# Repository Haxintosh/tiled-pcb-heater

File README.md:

# Tiled 3D printing bed
This project is a scalable, Klipper-compatible heated bed system designed for efficiency and flexibility. The bed is built from PCB-based heater tiles (≈100W each) that can be individually powered, allowing selective heating to reduce energy use. A central hub board, driven by an STM32 microcontroller, controls up to multiple channels with individual MOSFET switching and thermistor sensing.  

The project consists of 2 types of PCBs, the tiles and the power distribution boards.  

Currently there is a 150mm tile and a 8 channel power distribution board.  

## Images
Heater tile:  

Power distribution board:  

## Specs
The calculator can found here: https://www.desmos.com/calculator/dyaic1mb9s  

Per tile:
| Measurements 	| Value         	|
|--------------	|---------------	|
| Dimensions   	| 150mm x 150mm 	|
| Power			| ~110W @ 24v   	|
| Max Temp		| ~105°C*			|

> [!WARNING]
> The max operating temperature depends on the rated temperature of the connector. The thermal fuse blows at around 125°C to prevent thermal runaway, but the current chosen connector (MicroFit 3) is only rated to 105°C.

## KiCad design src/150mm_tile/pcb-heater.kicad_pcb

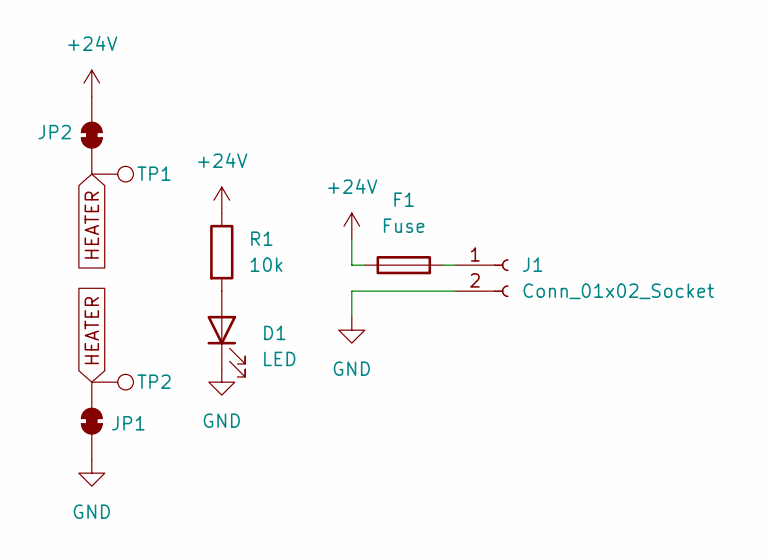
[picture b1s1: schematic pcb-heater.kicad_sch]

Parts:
D1: LED; LED_0603_1608Metric
F1: Fuse; thermal fuse
J1: Conn_01x02_Socket; Molex_Micro-Fit_3.0_43045-0218_2x01-1MP_P3.00mm_Vertical
JP1, JP2: SolderJumper_2_Bridged; SolderJumper-2_P1.3mm_Bridged_Pad1.0x1.5mm
R1: 10k; R_0603_1608Metric
TP1, TP2: TestPoint; TestPoint_Pad_1.0x1.0mm

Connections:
+24V: F1.1, JP2.1 (A), R1.1
GND: D1.1 (K), J1.2, JP1.1 (A)
HEATER: JP1.2 (B), JP2.2 (B), TP1.1, TP2.1
unnamed: D1.2 (A), R1.2
unnamed: F1.2, J1.1, J1.MP

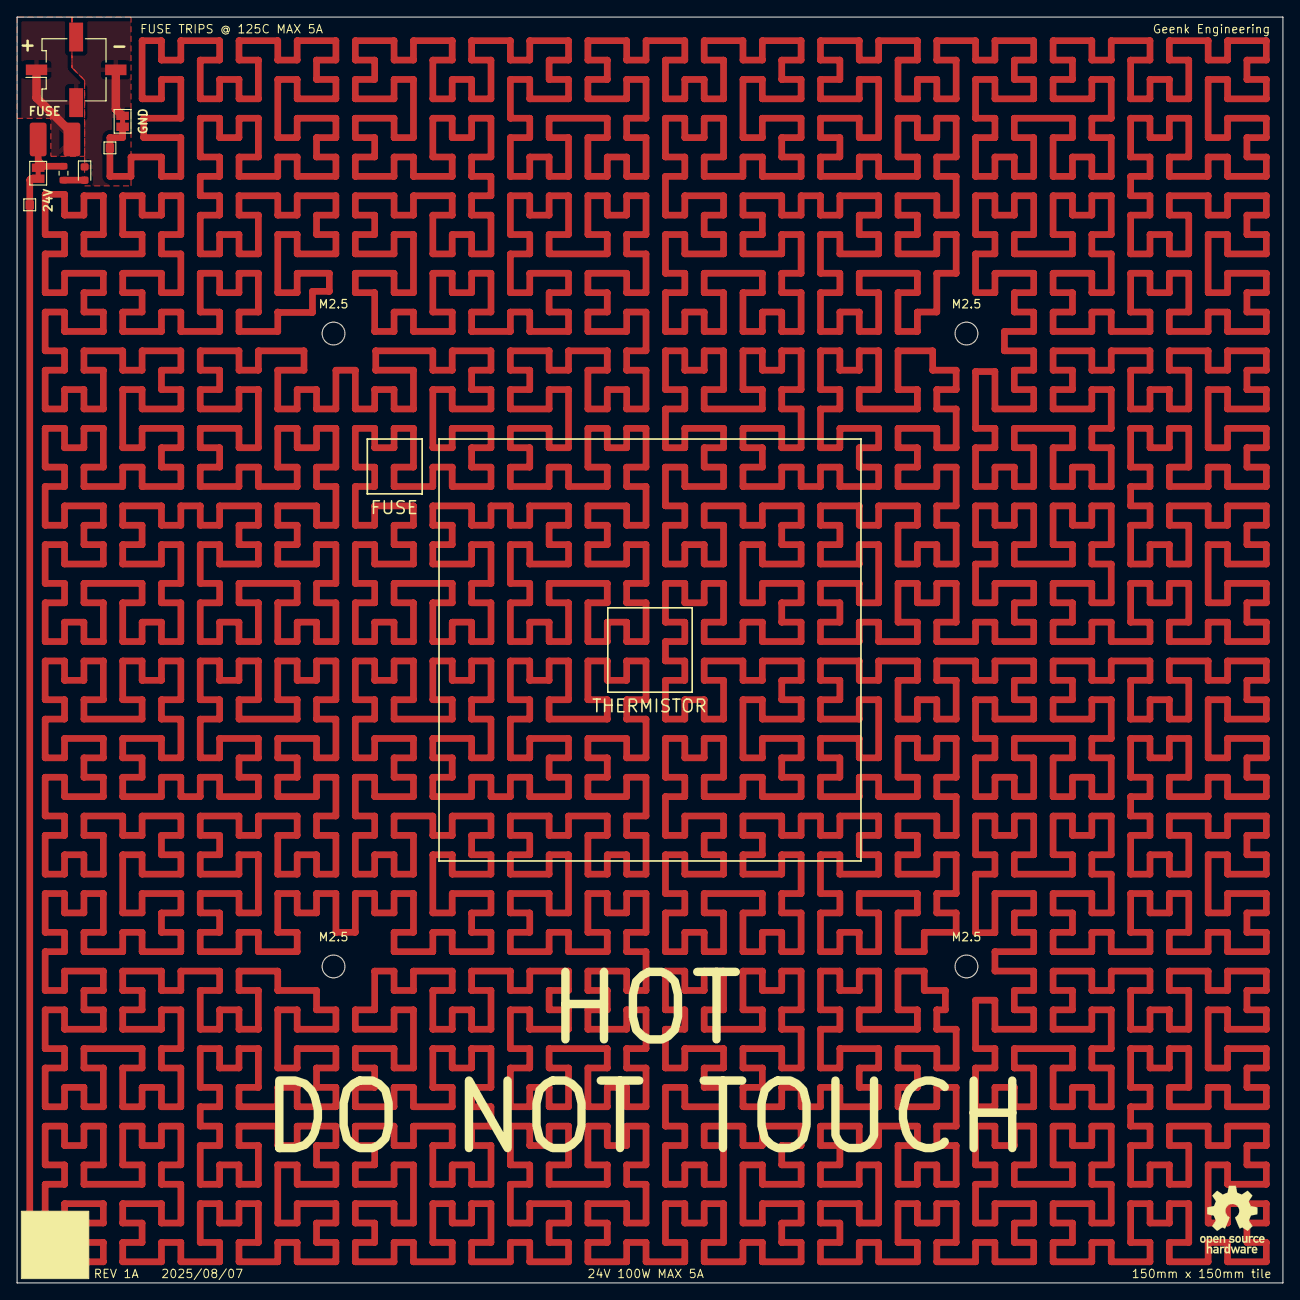
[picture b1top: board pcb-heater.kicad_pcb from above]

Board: 2 copper layers, 150.0 x 150.0 mm, 12 parts (0 on the bottom side), 5 nets.

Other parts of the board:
M2.5, M2.5#2, M2.5#3, M2.5#4: MountingHole_2.7mm_M2.5_DIN965

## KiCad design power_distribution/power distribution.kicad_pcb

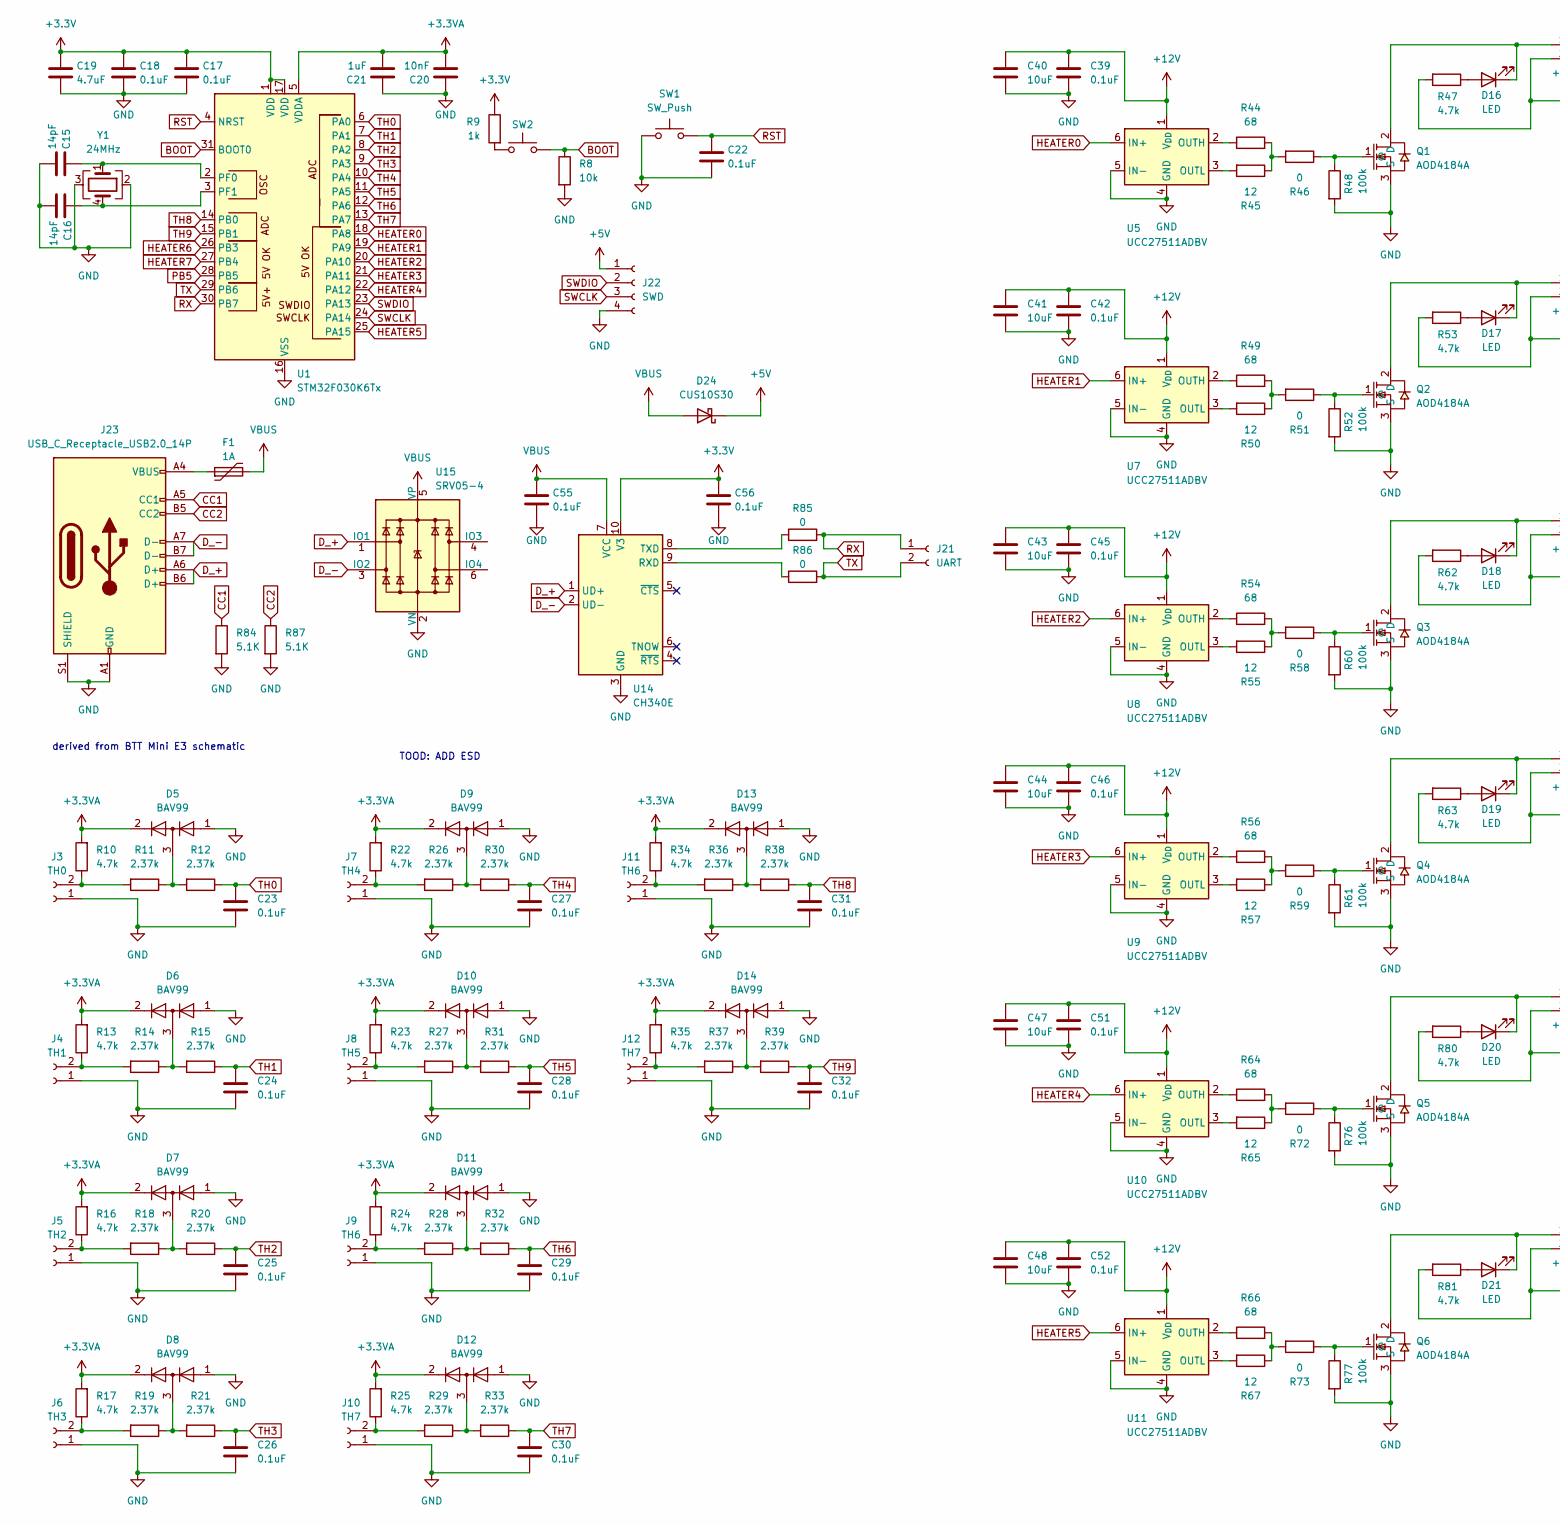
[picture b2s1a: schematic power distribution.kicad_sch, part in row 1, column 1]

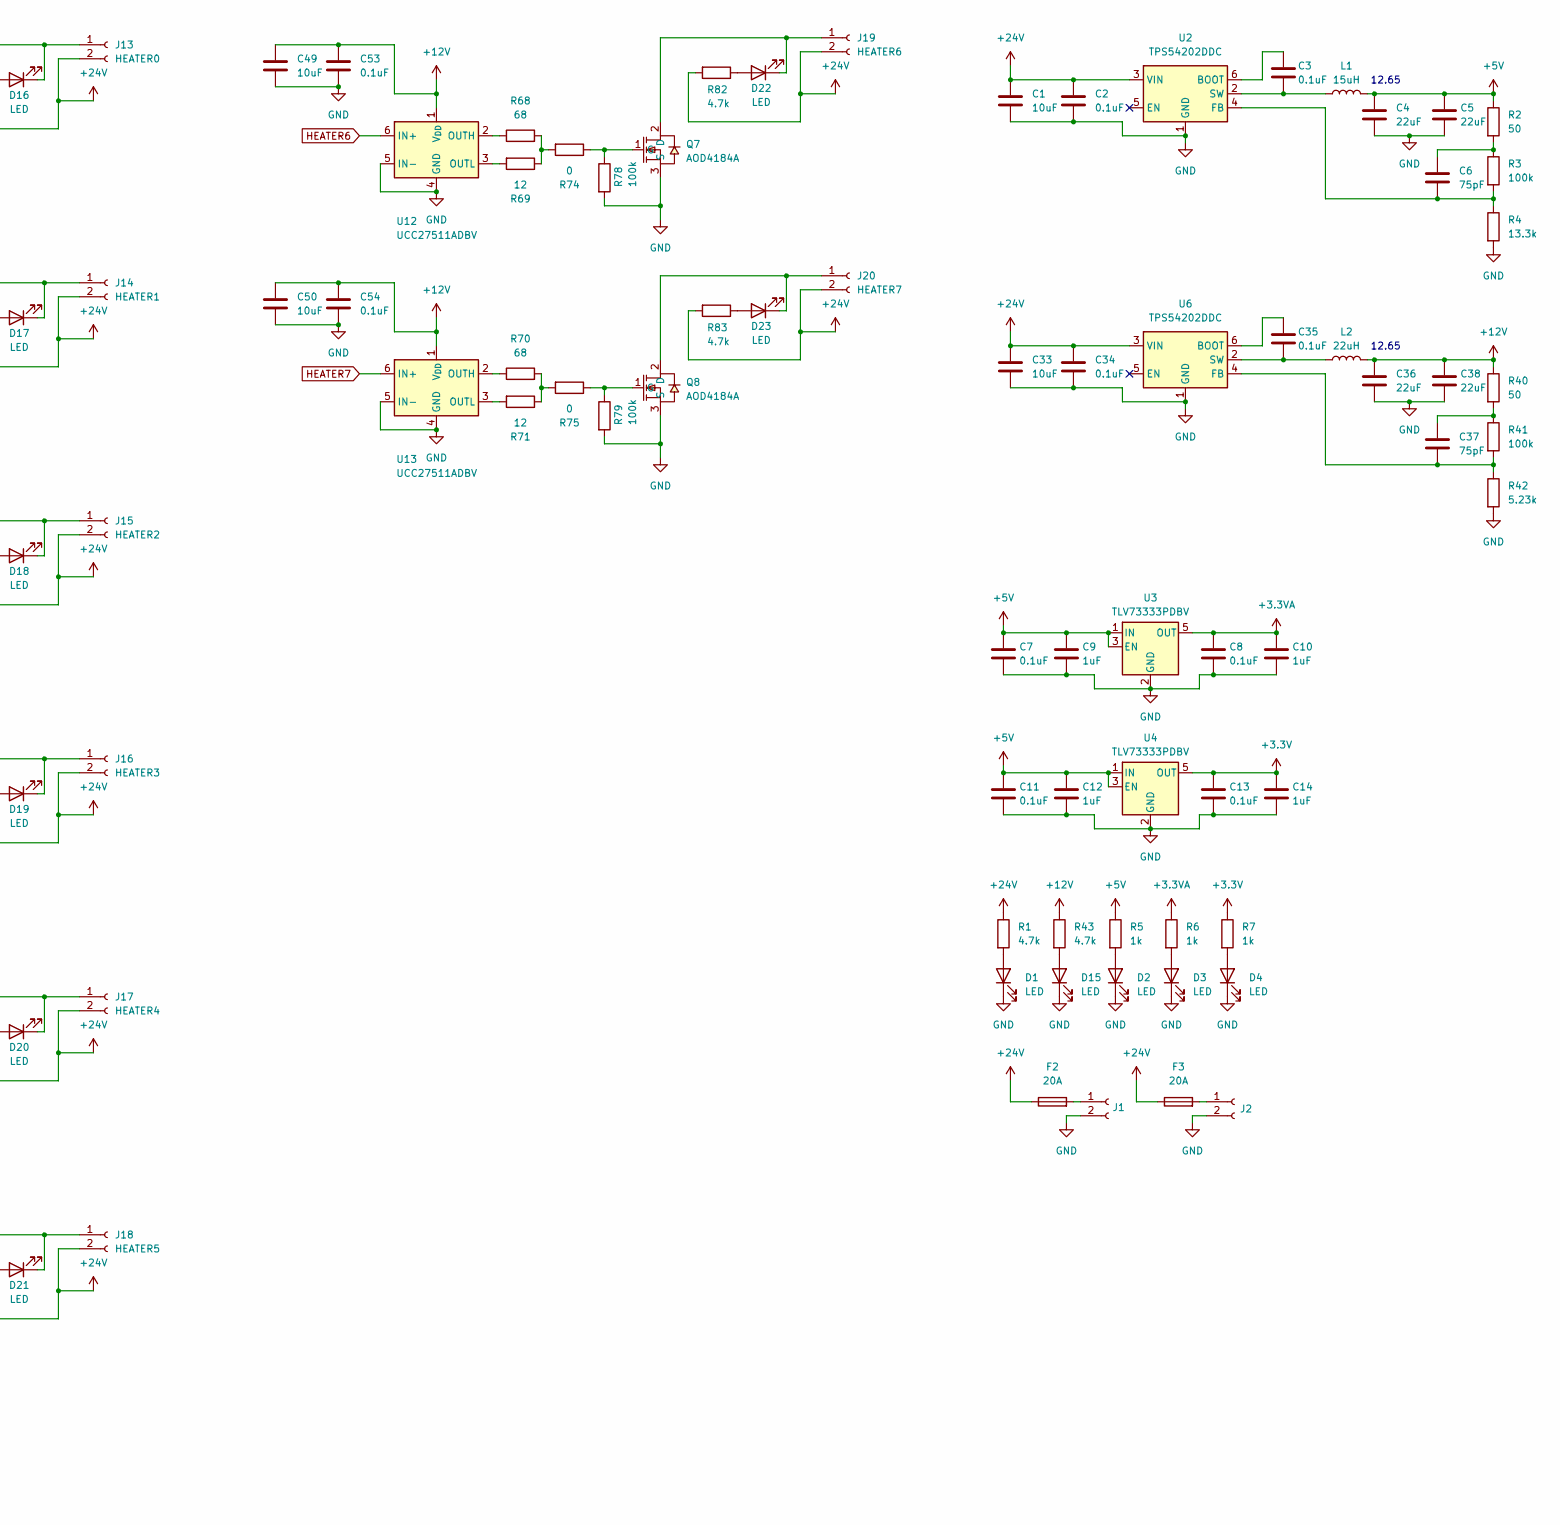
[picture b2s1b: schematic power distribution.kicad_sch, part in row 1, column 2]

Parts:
C1, C33, C40, C41, C43, C44, C47, C48, C49, C50: 10uF; C_0603_1608Metric
C2, C3, C7, C8, C11, C13, C17, C18, C22, C23, C24, C25, C26, C27, C28, C29, C30, C31, C32, C34, C35, C39, C42, C45, C46, C51, C52, C53, C54, C55, C56: 0.1uF; C_0603_1608Metric
C4, C5, C36, C38: 22uF; C_0603_1608Metric
C6, C37: 75pF; C_0402_1005Metric
C9, C10, C12, C14, C21: 1uF; C_0603_1608Metric
C15, C16: 14pF; C_0402_1005Metric
C19: 4.7uF; C_0603_1608Metric
C20: 10nF; C_0603_1608Metric
D1, D2, D3, D4, D15, D16, D17, D18, D19, D20, D21, D22, D23: LED; LED_0603_1608Metric
D5, D6, D7, D8, D9, D10, D11, D12, D13, D14: BAV99; SOT-23
D24: CUS10S30; D_SOD-323; lcsc C146335
F1: 1A; C_1812_4532Metric; lcsc C2649901
F2, F3: 20A; FUSE-TH_4P-L16.0-W6.7
J1, J2: Conn_01x02_Socket; CONN-TH_2P-P9.50_DBT50G-9.5-2P
J3: TH0; JST_XH_B2B-XH-A_1x02_P2.50mm_Vertical
J4: TH1; JST_XH_B2B-XH-A_1x02_P2.50mm_Vertical
J5: TH2; JST_XH_B2B-XH-A_1x02_P2.50mm_Vertical
J6: TH3; JST_XH_B2B-XH-A_1x02_P2.50mm_Vertical
J7: TH4; JST_XH_B2B-XH-A_1x02_P2.50mm_Vertical
J8: TH5; JST_XH_B2B-XH-A_1x02_P2.50mm_Vertical
J9, J11: TH6; JST_XH_B2B-XH-A_1x02_P2.50mm_Vertical
J10, J12: TH7; JST_XH_B2B-XH-A_1x02_P2.50mm_Vertical
J13: HEATER0; Molex_Micro-Fit_3.0_43045-0212_2x01_P3.00mm_Vertical
J14: HEATER1; Molex_Micro-Fit_3.0_43045-0212_2x01_P3.00mm_Vertical
J15: HEATER2; Molex_Micro-Fit_3.0_43045-0212_2x01_P3.00mm_Vertical
J16: HEATER3; Molex_Micro-Fit_3.0_43045-0212_2x01_P3.00mm_Vertical
J17: HEATER4; Molex_Micro-Fit_3.0_43045-0212_2x01_P3.00mm_Vertical
J18: HEATER5; Molex_Micro-Fit_3.0_43045-0212_2x01_P3.00mm_Vertical
J19: HEATER6; Molex_Micro-Fit_3.0_43045-0212_2x01_P3.00mm_Vertical
J20: HEATER7; Molex_Micro-Fit_3.0_43045-0212_2x01_P3.00mm_Vertical
J21: UART; JST_XH_B2B-XH-A_1x02_P2.50mm_Vertical
J22: SWD; JST_XH_B4B-XH-A_1x04_P2.50mm_Vertical
J23: USB_C_Receptacle_USB2.0_14P; USB_C_Receptacle_G-Switch_GT-USB-7010ASV
L1: 15uH; L_TechFuse_SL0650; lcsc C149585
L2: 22uH; L_Sunlord_MWSA0402S
Q1, Q2, Q3, Q4, Q5, Q6, Q7, Q8: AOD4184A; TO-252-2_L6.6-W6.1-P4.57-LS9.9-TL-CW; LCSC Part C99124
R1, R10, R13, R16, R17, R22, R23, R24, R25, R34, R35, R43, R47, R53, R62, R63, R80, R81, R82, R83: 4.7k; R_0603_1608Metric
R2, R40: 50; R_0402_1005Metric
R3, R41: 100k; R_0402_1005Metric
R4: 13.3k; R_0402_1005Metric
R5, R6, R7, R9: 1k; R_0603_1608Metric
R8: 10k; R_0603_1608Metric
R11, R12, R14, R15, R18, R19, R20, R21, R26, R27, R28, R29, R30, R31, R32, R33, R36, R37, R38, R39: 2.37k; R_0402_1005Metric
R42: 5.23k; R_0402_1005Metric
R44, R49, R54, R56, R64, R66, R68, R70: 68; R_1206_3216Metric
R45, R50, R55, R57, R65, R67, R69, R71: 12; R_1206_3216Metric
R46, R51, R58, R59, R72, R73, R74, R75, R85, R86: 0; R_1206_3216Metric
R48, R52, R60, R61, R76, R77, R78, R79: 100k; R_0603_1608Metric
R84, R87: 5.1K; R_0402_1005Metric
SW1: SW_Push; SW-SMD_L3.9-W3.0-P4.45
SW2: SW_Push; SW-SMD_L3.9-W3.0-P4.45; lcsc C455280
U1: STM32F030K6Tx; LQFP-32_7x7mm_P0.8mm
U2, U6: TPS54202DDC; SOT-23-6
U3, U4: TLV73333PDBV; SOT-23-5
U5, U7, U8, U9, U10, U11, U12, U13: UCC27511ADBV; SOT-23-6
U14: CH340E; MSOP-10_3x3mm_P0.5mm
U15: SRV05-4; SOT-23-6
Y1: 24MHz; Crystal_SMD_3225-4Pin_3.2x2.5mm

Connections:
+3.3V: C13.1, C14.1, C17.1, C18.1, C19.1, C56.1, R7.1, R9.1, U1.1 (VDD), U1.17 (VDD), U4.5 (OUT), U14.10 (V3)
+3.3VA: C8.1, C10.1, C20.2, C21.2, D5.2 (A), D6.2 (A), D7.2 (A), D8.2 (A), D9.2 (A), D10.2 (A), D11.2 (A), D12.2 (A), D13.2 (A), D14.2 (A), R6.1, R10.2, R13.2, R16.2, R17.2, R22.2, R23.2, R24.2, R25.2, R34.2, R35.2, U1.5 (VDDA), U3.5 (OUT)
+5V: C4.1, C5.1, C7.1, C9.1, C11.1, C12.1, D24.1 (K), J22.1, L1.2, R2.1, R5.1, U3.1 (IN), U3.3 (EN), U4.1 (IN), U4.3 (EN)
+12V: C36.1, C38.1, C39.1, C40.1, C41.1, C42.1, C43.1, C44.1, C45.1, C46.1, C47.1, C48.1, C49.1, C50.1, C51.1, C52.1, C53.1, C54.1, L2.2, R40.1, R43.1, U5.1 (V_{DD}), U7.1 (V_{DD}), U8.1 (V_{DD}), U9.1 (V_{DD}), U10.1 (V_{DD}), U11.1 (V_{DD}), U12.1 (V_{DD}), U13.1 (V_{DD})
+24V: C1.1, C2.1, C33.1, C34.1, F2.1, F3.1, J13.2, J14.2, J15.2, J16.2, J17.2, J18.2, J19.2, J20.2, R1.1, R47.2, R53.2, R62.2, R63.2, R80.2, R81.2, R82.2, R83.2, U2.3 (VIN), U6.3 (VIN)
BOOT: R8.1, SW2.2, U1.31 (BOOT0)
CC1: J23.A5 (CC1), R84.1
CC2: J23.B5 (CC2), R87.1
D_+: J23.A6 (D+), J23.B6 (D+), U14.1 (UD+), U15.1 (IO1)
D_-: J23.A7 (D-), J23.B7 (D-), U14.2 (UD-), U15.3 (IO2)
GND: C1.2, C2.2, C4.2, C5.2, C7.2, C8.2, C9.2, C10.2, C11.2, C12.2, C13.2, C14.2, C15.2, C16.2, C17.2, C18.2, C19.2, C20.1, C21.1, C22.2, C23.2, C24.2, C25.2, C26.2, C27.2, C28.2, C29.2, C30.2, C31.2, C32.2, C33.2, C34.2, C36.2, C38.2, C39.2, C40.2, C41.2, C42.2, C43.2, C44.2, C45.2, C46.2, C47.2, C48.2, C49.2, C50.2, C51.2, C52.2, C53.2, C54.2, C55.2, C56.2, D1.1 (K), D2.1 (K), D3.1 (K), D4.1 (K), D5.1 (K), D6.1 (K), D7.1 (K), D8.1 (K), D9.1 (K), D10.1 (K), D11.1 (K), D12.1 (K), D13.1 (K), D14.1 (K), D15.1 (K), J1.2, J2.2, J3.1, J4.1, J5.1, J6.1, J7.1, J8.1, J9.1, J10.1, J11.1, J12.1, J22.4, J23.A1 (GND), J23.A12 (GND), J23.B1 (GND), J23.B12 (GND), J23.S1 (SHIELD), Q1.3 (S), Q2.3 (S), Q3.3 (S), Q4.3 (S), Q5.3 (S), Q6.3 (S), Q7.3 (S), Q8.3 (S), R4.2, R8.2, R42.2, R48.2, R52.2, R60.2, R61.2, R76.2, R77.2, R78.2, R79.2, R84.2, R87.2, SW1.1, U1.16 (VSS), U1.32 (VSS), U2.1 (GND), U3.2 (GND), U4.2 (GND), U5.4 (GND), U5.5 (IN-), U6.1 (GND), U7.4 (GND), U7.5 (IN-), U8.4 (GND), U8.5 (IN-), U9.4 (GND), U9.5 (IN-), U10.4 (GND), U10.5 (IN-), U11.4 (GND), U11.5 (IN-), U12.4 (GND), U12.5 (IN-), U13.4 (GND), U13.5 (IN-), U14.3 (GND), U15.2 (VN), Y1.2, Y1.3
HEATER0: U1.18 (PA8), U5.6 (IN+)
HEATER1: U1.19 (PA9), U7.6 (IN+)
HEATER2: U1.20 (PA10), U8.6 (IN+)
HEATER3: U1.21 (PA11), U9.6 (IN+)
HEATER4: U1.22 (PA12), U10.6 (IN+)
HEATER5: U1.25 (PA15), U11.6 (IN+)
HEATER6: U1.26 (PB3), U12.6 (IN+)
HEATER7: U1.27 (PB4), U13.6 (IN+)
unnamed: C6.1, R2.2, R3.1
unnamed: C37.1, R40.2, R41.1
unnamed: D1.2 (A), R1.2
unnamed: D2.2 (A), R5.2
unnamed: D3.2 (A), R6.2
unnamed: D4.2 (A), R7.2
unnamed: D5.3 (K), R11.1, R12.2
unnamed: D6.3 (K), R14.1, R15.2
unnamed: D7.3 (K), R18.1, R20.2
unnamed: D8.3 (K), R19.1, R21.2
unnamed: D9.3 (K), R26.1, R30.2
unnamed: D10.3 (K), R27.1, R31.2
unnamed: D11.3 (K), R28.1, R32.2
unnamed: D12.3 (K), R29.1, R33.2
unnamed: D13.3 (K), R36.1, R38.2
unnamed: D14.3 (K), R37.1, R39.2
unnamed: D15.2 (A), R43.2
unnamed: D16.2 (A), R47.1
unnamed: D16.1 (K), J13.1, Q1.2 (D)
unnamed: D17.2 (A), R53.1
unnamed: D17.1 (K), J14.1, Q2.2 (D)
unnamed: D18.2 (A), R62.1
unnamed: D18.1 (K), J15.1, Q3.2 (D)
unnamed: D19.2 (A), R63.1
unnamed: D19.1 (K), J16.1, Q4.2 (D)
unnamed: D20.2 (A), R80.1
unnamed: D20.1 (K), J17.1, Q5.2 (D)
unnamed: D21.2 (A), R81.1
unnamed: D21.1 (K), J18.1, Q6.2 (D)
unnamed: D22.2 (A), R82.1
unnamed: D22.1 (K), J19.1, Q7.2 (D)
unnamed: D23.2 (A), R83.1
unnamed: D23.1 (K), J20.1, Q8.2 (D)
unnamed: F1.1, J23.A4 (VBUS), J23.A9 (VBUS), J23.B4 (VBUS), J23.B9 (VBUS)
unnamed: F2.2, J1.1
unnamed: F3.2, J2.1
unnamed: J3.2, R10.1, R11.2
unnamed: J4.2, R13.1, R14.2
unnamed: J5.2, R16.1, R18.2
unnamed: J6.2, R17.1, R19.2
unnamed: J7.2, R22.1, R26.2
unnamed: J8.2, R23.1, R27.2
unnamed: J9.2, R24.1, R28.2
unnamed: J10.2, R25.1, R29.2
unnamed: J11.2, R34.1, R36.2
unnamed: J12.2, R35.1, R37.2
unnamed: Q1.1 (G), R46.1, R48.1
unnamed: Q2.1 (G), R51.1, R52.1
unnamed: Q3.1 (G), R58.1, R60.1
unnamed: Q4.1 (G), R59.1, R61.1
unnamed: Q5.1 (G), R72.1, R76.1
unnamed: Q6.1 (G), R73.1, R77.1
unnamed: Q7.1 (G), R74.1, R78.1
unnamed: Q8.1 (G), R75.1, R79.1
unnamed: R9.2, SW2.1
unnamed: R44.2, R45.1, R46.2
unnamed: R49.2, R50.1, R51.2
unnamed: R54.2, R55.1, R58.2
unnamed: R56.2, R57.1, R59.2
unnamed: R64.2, R65.1, R72.2
unnamed: R66.2, R67.1, R73.2
unnamed: R68.2, R69.1, R74.2
unnamed: R70.2, R71.1, R75.2
unnamed: C15.1, U1.2 (PF0), Y1.1
unnamed: C16.1, U1.3 (PF1), Y1.4
unnamed: C3.1, U2.6 (BOOT)
unnamed: C6.2, R3.2, R4.1, U2.4 (FB)
unnamed: C3.2, L1.1, U2.2 (SW)
unnamed: R44.1, U5.2 (OUTH)
unnamed: R45.2, U5.3 (OUTL)
unnamed: C35.1, U6.6 (BOOT)
unnamed: C37.2, R41.2, R42.1, U6.4 (FB)
unnamed: C35.2, L2.1, U6.2 (SW)
unnamed: R49.1, U7.2 (OUTH)
unnamed: R50.2, U7.3 (OUTL)
unnamed: R54.1, U8.2 (OUTH)
unnamed: R55.2, U8.3 (OUTL)
unnamed: R56.1, U9.2 (OUTH)
unnamed: R57.2, U9.3 (OUTL)
unnamed: R64.1, U10.2 (OUTH)
unnamed: R65.2, U10.3 (OUTL)
unnamed: R66.1, U11.2 (OUTH)
unnamed: R67.2, U11.3 (OUTL)
unnamed: R68.1, U12.2 (OUTH)
unnamed: R69.2, U12.3 (OUTL)
unnamed: R70.1, U13.2 (OUTH)
unnamed: R71.2, U13.3 (OUTL)
unnamed: R86.1, U14.9 (RXD)
unnamed: R85.1, U14.8 (TXD)
RST: C22.1, SW1.2, U1.4 (NRST)
RX: J21.1, R85.2, U1.30 (PB7)
SWCLK: J22.3, U1.24 (PA14)
SWDIO: J22.2, U1.23 (PA13)
TH0: C23.1, R12.1, U1.6 (PA0)
TH1: C24.1, R15.1, U1.7 (PA1)
TH2: C25.1, R20.1, U1.8 (PA2)
TH3: C26.1, R21.1, U1.9 (PA3)
TH4: C27.1, R30.1, U1.10 (PA4)
TH5: C28.1, R31.1, U1.11 (PA5)
TH6: C29.1, R32.1, U1.12 (PA6)
TH7: C30.1, R33.1, U1.13 (PA7)
TH8: C31.1, R38.1, U1.14 (PB0)
TH9: C32.1, R39.1, U1.15 (PB1)
TX: J21.2, R86.2, U1.29 (PB6)
VBUS: C55.1, D24.2 (A), F1.2, U14.7 (VCC), U15.5 (VP)

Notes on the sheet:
derived from BTT Mini E3 schematic
12.65
TOOD: ADD ESD

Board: 2 copper layers, 221 parts (0 on the bottom side), 124 nets, no tracks yet.

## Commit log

2025-08-07 chore: initial commit
2025-08-08 milestone: tile pcb done
2025-08-11 milestone: power distribution schematic done
2025-08-21 milestone: finished PCB design of the Power Distribution Board
2025-08-21 fix: fixed uart connections, usb flashing requires flashing via UART on PA9/PA10
2025-08-27 chore: update github journal with obsidian journal
2025-08-27 chore: fix log numbering
2025-08-28 chore: add images
2025-08-28 chore: cleanuo
2025-08-28 chore:test image
2025-08-28 chore: add images to journal
2025-08-28 chore: add missing images
2025-08-28 chore: add missing images to journal
2025-08-28 chore: Add PCB render image to README
    Added an image render of the power distribution PCB to the README.
2025-08-28 chore: update 150mm tile fabrication outputs
2025-08-28 chore: update for submission
2025-08-28 chore: remove redundant files
2025-08-28 chore: fix formating
2025-09-01 chore: Add CERN Open Hardware Licence
    Added CERN Open Hardware Licence Version 2 - Permissive to the project.
2025-09-02 chore: add desc
    Expanded project description and added specifications for the heated bed system.
2025-09-02 chore: add hero
2025-09-04 chore: add heater render image
2025-09-04 chore: add images to readme
